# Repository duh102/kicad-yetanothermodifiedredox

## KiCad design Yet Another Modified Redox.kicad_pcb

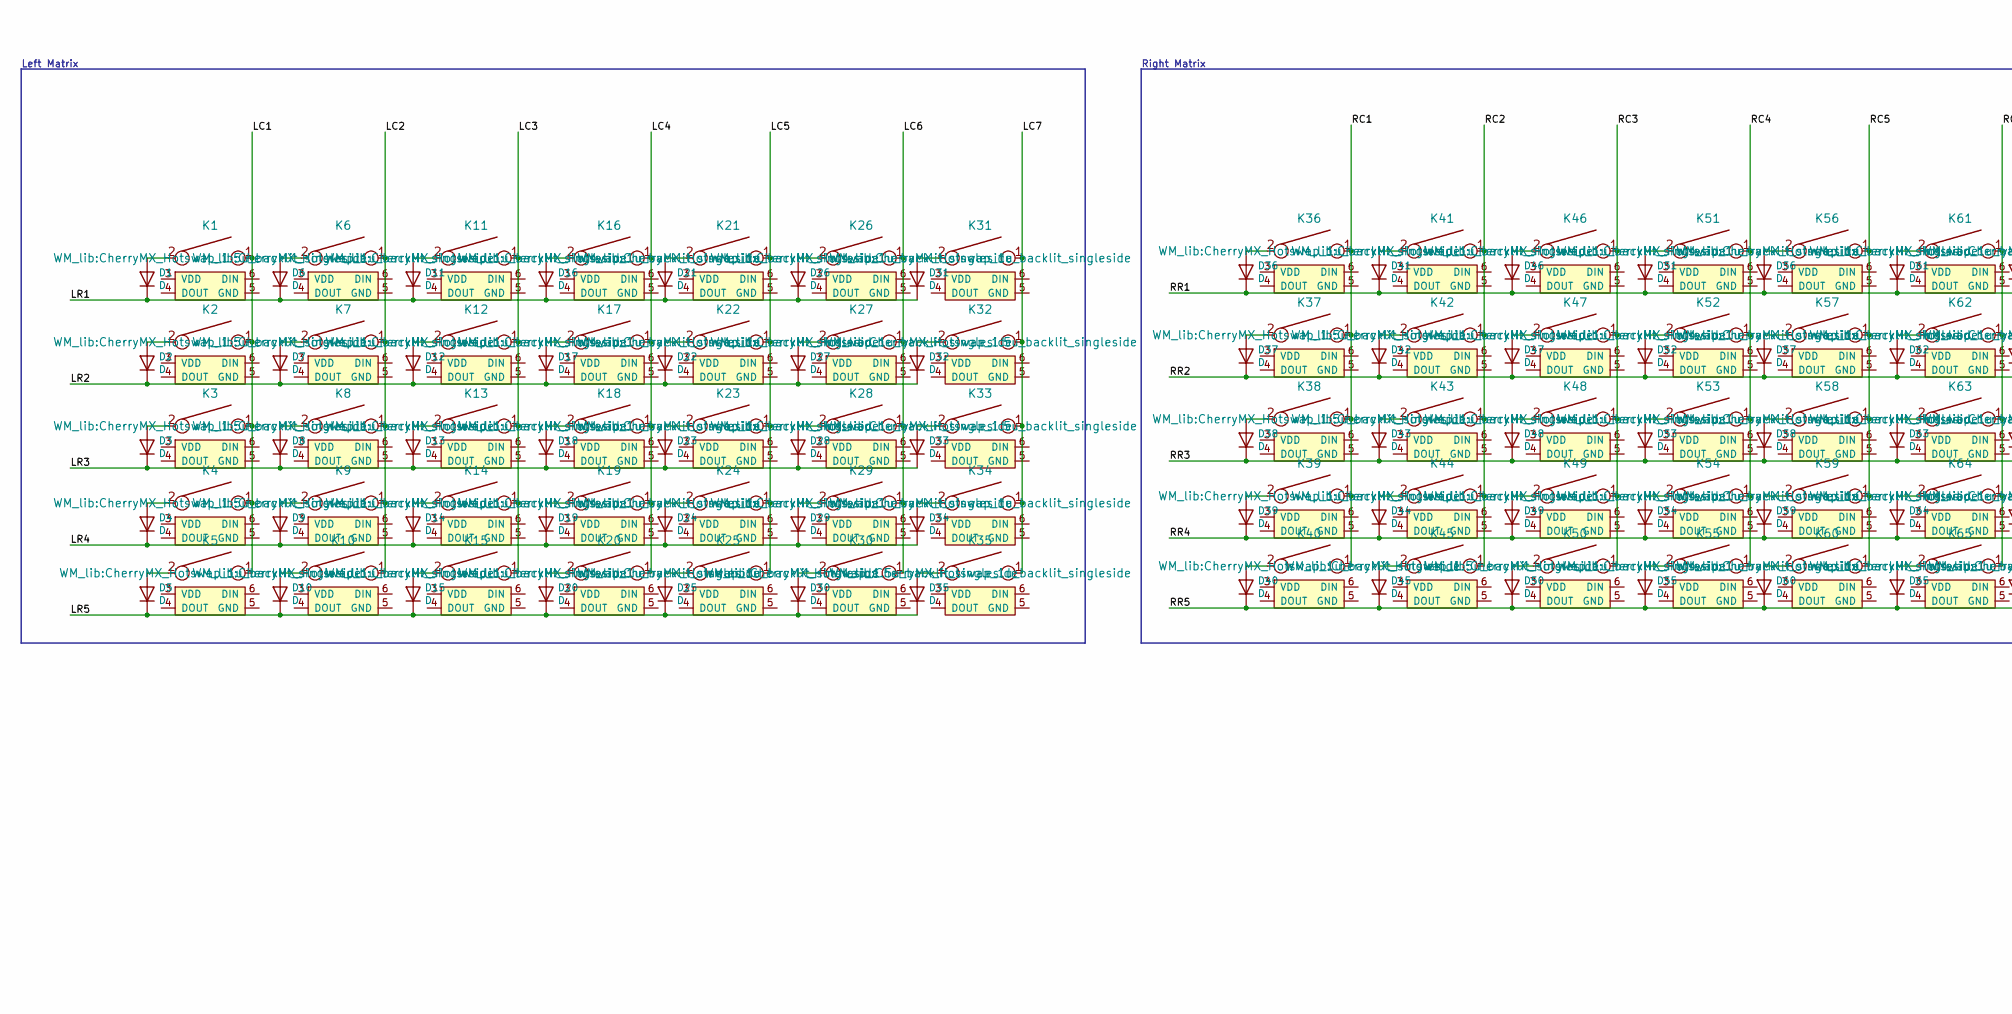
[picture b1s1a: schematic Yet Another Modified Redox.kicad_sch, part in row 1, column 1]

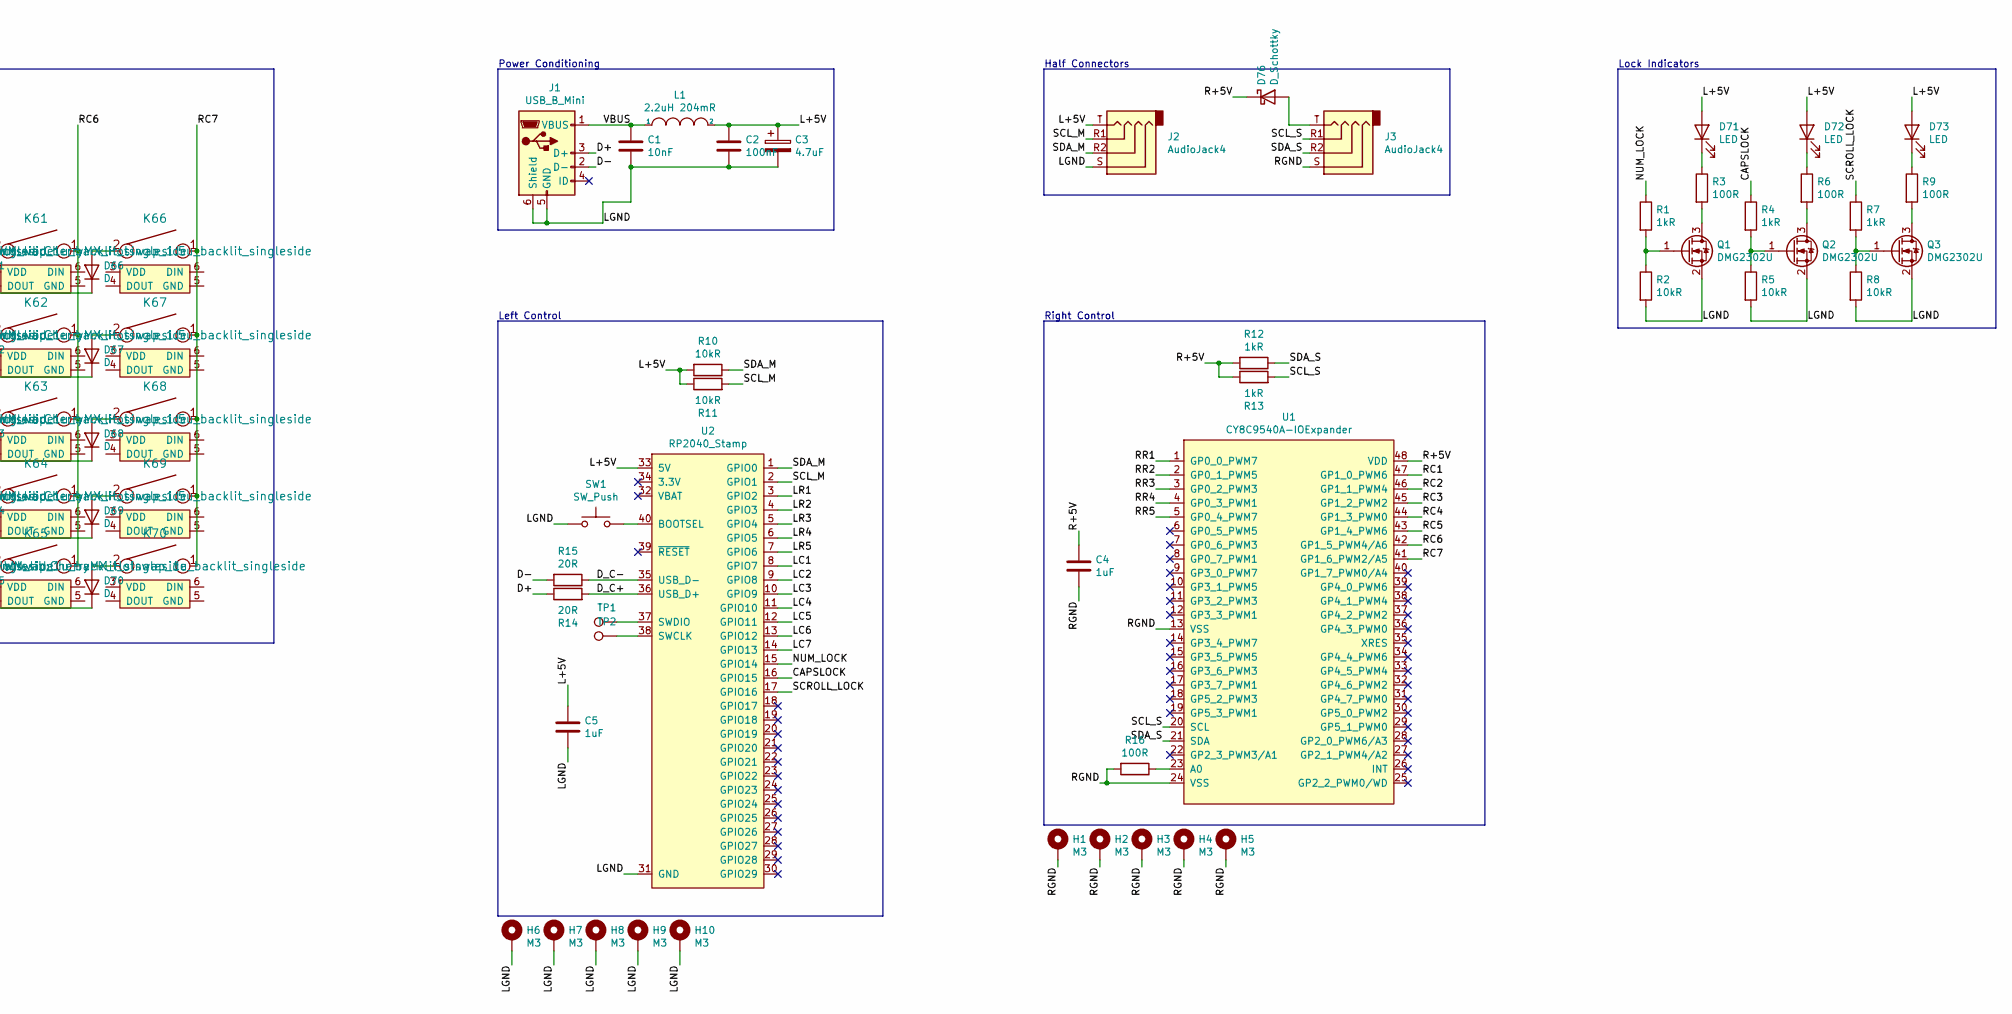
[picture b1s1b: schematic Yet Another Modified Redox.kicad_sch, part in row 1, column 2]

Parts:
C1: 10nF; C_0603_1608Metric
C2: 100nF; C_0603_1608Metric
C3: 4.7uF; CP_Radial_D4.0mm_P2.00mm
C4, C5: 1uF; C_0805_2012Metric
D1, D2, D3, D4, D5, D6, D7, D8, D9, D10, D11, D12, D13, D14, D15, D16, D17, D18, D19, D20, D21, D22, D23, D24, D25, D26, D27, D28, D29, D30, D31, D32, D33, D34, D35, D36, D37, D38, D39, D40, D41, D42, D43, D44, D45, D46, D47, D48, D49, D50, D51, D52, D53, D54, D55, D56, D57, D58, D59, D60, D61, D62, D63, D64, D65, D66, D67, D68, D69, D70: D; D3_TH_SMD_singleside
D71, D72, D73: LED; LED_D3.0mm
D76: D_Schottky; D_SOD-123
H1, H2, H3, H4, H5, H6, H7, H8, H9, H10: M3; MountingHole_3.2mm_M3_ISO14580_Pad
J1: USB_B_Mini; USB_Mini_B_Female_690-005-299-043
J2, J3: AudioJack4; TRRS-PJ-320A
K1, K2, K3, K4, K30, K32, K33, K37, K38, K45, K66, K67, K68, K69: KEYSW; CherryMX_Hotswap_1.5u_backlit_singleside
K5, K6, K7, K8, K9, K10, K11, K12, K13, K14, K15, K16, K17, K18, K19, K20, K21, K22, K23, K24, K25, K26, K27, K28, K29, K31, K34, K35, K36, K39, K40, K41, K42, K43, K44, K46, K47, K48, K49, K50, K51, K52, K53, K54, K55, K56, K57, K58, K59, K60, K61, K62, K63, K64, K65, K70: KEYSW; CherryMX_Hotswap_1u_backlit_singleside
L1: 2.2uH 204mR; L_0805_2012Metric_Pad1.15x1.40mm_HandSolder
Q1, Q2, Q3: DMG2302U; SOT-23
R1, R4, R7, R12, R13: 1kR; R_0805_2012Metric
R2, R5, R8, R10, R11: 10kR; R_0805_2012Metric
R3, R6, R9, R16: 100R; R_0805_2012Metric
R14, R15: 20R; R_0805_2012Metric
SW1: SW_Push; SW_SPST_SKQG_WithoutStem
TP1: TP; TestPoint_Pad_D2.0mm
TP2: TestPoint; TestPoint_Pad_D2.0mm
U1: CY8C9540A-IOExpander; SSOP-48_7.5x15.9mm_P0.635mm
U2: RP2040_Stamp; RP2040_Stamp_SMD

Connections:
/CAPSLOCK: R4.1, U2.16 (GPIO15)
/D+: J1.3 (D+), R14.1
/D-: J1.2 (D-), R15.2
/D_C+: R14.2, U2.36 (USB_D+)
/D_C-: R15.1, U2.35 (USB_D-)
/L+5V: C2.1, C3.1, C5.1, D71.2 (A), D72.2 (A), D73.2 (A), J2.T, L1.2, R10.2, R11.1, U2.33 (5V)
/LC1: K1.1, K2.1, K3.1, K4.1, K5.1, U2.8 (GPIO7)
/LC2: K6.1, K7.1, K8.1, K9.1, K10.1, U2.9 (GPIO8)
/LC3: K11.1, K12.1, K13.1, K14.1, K15.1, U2.10 (GPIO9)
/LC4: K16.1, K17.1, K18.1, K19.1, K20.1, U2.11 (GPIO10)
/LC5: K21.1, K22.1, K23.1, K24.1, K25.1, U2.12 (GPIO11)
/LC6: K26.1, K27.1, K28.1, K29.1, K30.1, U2.13 (GPIO12)
/LC7: K31.1, K32.1, K33.1, K34.1, K35.1, U2.14 (GPIO13)
/LGND: C1.2, C2.2, C3.2, C5.2, H6.1, H7.1, H8.1, H9.1, H10.1, J1.5 (GND), J1.6 (Shield), J2.S, Q1.2 (S), Q2.2 (S), Q3.2 (S), R2.2, R5.2, R8.2, SW1.1, U2.31 (GND)
/LR1: D1.1 (K), D6.1 (K), D11.1 (K), D16.1 (K), D21.1 (K), D26.1 (K), D31.1 (K), U2.3 (GPIO2)
/LR2: D2.1 (K), D7.1 (K), D12.1 (K), D17.1 (K), D22.1 (K), D27.1 (K), D32.1 (K), U2.4 (GPIO3)
/LR3: D3.1 (K), D8.1 (K), D13.1 (K), D18.1 (K), D23.1 (K), D28.1 (K), D33.1 (K), U2.5 (GPIO4)
/LR4: D4.1 (K), D9.1 (K), D14.1 (K), D19.1 (K), D24.1 (K), D29.1 (K), D34.1 (K), U2.6 (GPIO5)
/LR5: D5.1 (K), D10.1 (K), D15.1 (K), D20.1 (K), D25.1 (K), D30.1 (K), D35.1 (K), U2.7 (GPIO6)
/NUM_LOCK: R1.1, U2.15 (GPIO14)
/R+5V: C4.1, D76.1 (K), R12.2, R13.1, U1.48 (VDD)
/RC1: K36.1, K37.1, K38.1, K39.1, K40.1, U1.47 (GP1_0_PWM6)
/RC2: K41.1, K42.1, K43.1, K44.1, K45.1, U1.46 (GP1_1_PWM4)
/RC3: K46.1, K47.1, K48.1, K49.1, K50.1, U1.45 (GP1_2_PWM2)
/RC4: K51.1, K52.1, K53.1, K54.1, K55.1, U1.44 (GP1_3_PWM0)
/RC5: K56.1, K57.1, K58.1, K59.1, K60.1, U1.43 (GP1_4_PWM6)
/RC6: K61.1, K62.1, K63.1, K64.1, K65.1, U1.42 (GP1_5_PWM4/A6)
/RC7: K66.1, K67.1, K68.1, K69.1, K70.1, U1.41 (GP1_6_PWM2/A5)
/RGND: C4.2, H1.1, H2.1, H3.1, H4.1, H5.1, J3.S, R16.2, U1.13 (VSS), U1.24 (VSS)
/RR1: D36.1 (K), D41.1 (K), D46.1 (K), D51.1 (K), D56.1 (K), D61.1 (K), D66.1 (K), U1.1 (GP0_0_PWM7)
/RR2: D37.1 (K), D42.1 (K), D47.1 (K), D52.1 (K), D57.1 (K), D62.1 (K), D67.1 (K), U1.2 (GP0_1_PWM5)
/RR3: D38.1 (K), D43.1 (K), D48.1 (K), D53.1 (K), D58.1 (K), D63.1 (K), D68.1 (K), U1.3 (GP0_2_PWM3)
/RR4: D39.1 (K), D44.1 (K), D49.1 (K), D54.1 (K), D59.1 (K), D64.1 (K), D69.1 (K), U1.4 (GP0_3_PWM1)
/RR5: D40.1 (K), D45.1 (K), D50.1 (K), D55.1 (K), D60.1 (K), D65.1 (K), D70.1 (K), U1.5 (GP0_4_PWM7)
/SCL_M: J2.R1, R11.2, U2.2 (GPIO1)
/SCL_S: J3.R1, R13.2, U1.20 (SCL)
/SCROLL_LOCK: R7.1, U2.17 (GPIO16)
/SDA_M: J2.R2, R10.1, U2.1 (GPIO0)
/SDA_S: J3.R2, R12.1, U1.21 (SDA)
/VBUS: C1.1, J1.1 (VBUS), L1.1
unnamed: D1.2 (A), K1.2
unnamed: D2.2 (A), K2.2
unnamed: D3.2 (A), K3.2
unnamed: D4.2 (A), K4.2
unnamed: D5.2 (A), K5.2
unnamed: D6.2 (A), K6.2
unnamed: D7.2 (A), K7.2
unnamed: D8.2 (A), K8.2
unnamed: D9.2 (A), K9.2
unnamed: D10.2 (A), K10.2
unnamed: D11.2 (A), K11.2
unnamed: D12.2 (A), K12.2
unnamed: D13.2 (A), K13.2
unnamed: D14.2 (A), K14.2
unnamed: D15.2 (A), K15.2
unnamed: D16.2 (A), K16.2
unnamed: D17.2 (A), K17.2
unnamed: D18.2 (A), K18.2
unnamed: D19.2 (A), K19.2
unnamed: D20.2 (A), K20.2
unnamed: D21.2 (A), K21.2
unnamed: D22.2 (A), K22.2
unnamed: D23.2 (A), K23.2
unnamed: D24.2 (A), K24.2
unnamed: D25.2 (A), K25.2
unnamed: D26.2 (A), K26.2
unnamed: D27.2 (A), K27.2
unnamed: D28.2 (A), K28.2
unnamed: D29.2 (A), K29.2
unnamed: D30.2 (A), K30.2
unnamed: D31.2 (A), K31.2
unnamed: D32.2 (A), K32.2
unnamed: D33.2 (A), K33.2
unnamed: D34.2 (A), K34.2
unnamed: D35.2 (A), K35.2
unnamed: D36.2 (A), K36.2
unnamed: D37.2 (A), K37.2
unnamed: D38.2 (A), K38.2
unnamed: D39.2 (A), K39.2
unnamed: D40.2 (A), K40.2
unnamed: D41.2 (A), K41.2
unnamed: D42.2 (A), K42.2
unnamed: D43.2 (A), K43.2
unnamed: D44.2 (A), K44.2
unnamed: D45.2 (A), K45.2
unnamed: D46.2 (A), K46.2
unnamed: D47.2 (A), K47.2
unnamed: D48.2 (A), K48.2
unnamed: D49.2 (A), K49.2
unnamed: D50.2 (A), K50.2
unnamed: D51.2 (A), K51.2
unnamed: D52.2 (A), K52.2
unnamed: D53.2 (A), K53.2
unnamed: D54.2 (A), K54.2
unnamed: D55.2 (A), K55.2
unnamed: D56.2 (A), K56.2
unnamed: D57.2 (A), K57.2
unnamed: D58.2 (A), K58.2
unnamed: D59.2 (A), K59.2
unnamed: D60.2 (A), K60.2
unnamed: D61.2 (A), K61.2
unnamed: D62.2 (A), K62.2
unnamed: D63.2 (A), K63.2
unnamed: D64.2 (A), K64.2
unnamed: D65.2 (A), K65.2
unnamed: D66.2 (A), K66.2
unnamed: D67.2 (A), K67.2
unnamed: D68.2 (A), K68.2
unnamed: D69.2 (A), K69.2
unnamed: D70.2 (A), K70.2
unnamed: D71.1 (K), R3.1
unnamed: D72.1 (K), R6.1
unnamed: D73.1 (K), R9.1
unnamed: D76.2 (A), J3.T
unnamed: Q1.1 (G), R1.2, R2.1
unnamed: Q1.3 (D), R3.2
unnamed: Q2.1 (G), R4.2, R5.1
unnamed: Q2.3 (D), R6.2
unnamed: Q3.1 (G), R7.2, R8.1
unnamed: Q3.3 (D), R9.2
unnamed: R16.1, U1.23 (A0)
unnamed: SW1.2, U2.40 (BOOTSEL)
unnamed: TP1.1, U2.37 (SWDIO)
unnamed: TP2.1, U2.38 (SWCLK)

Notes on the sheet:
Half Connectors
Power Conditioning
Left Control
Right Control
Right Matrix
Lock Indicators
Left Matrix

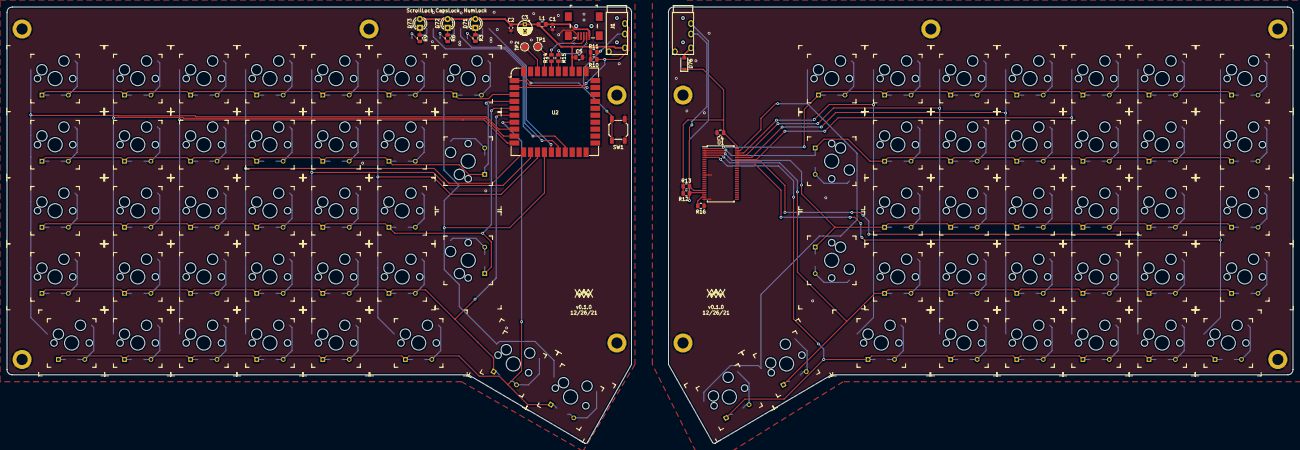
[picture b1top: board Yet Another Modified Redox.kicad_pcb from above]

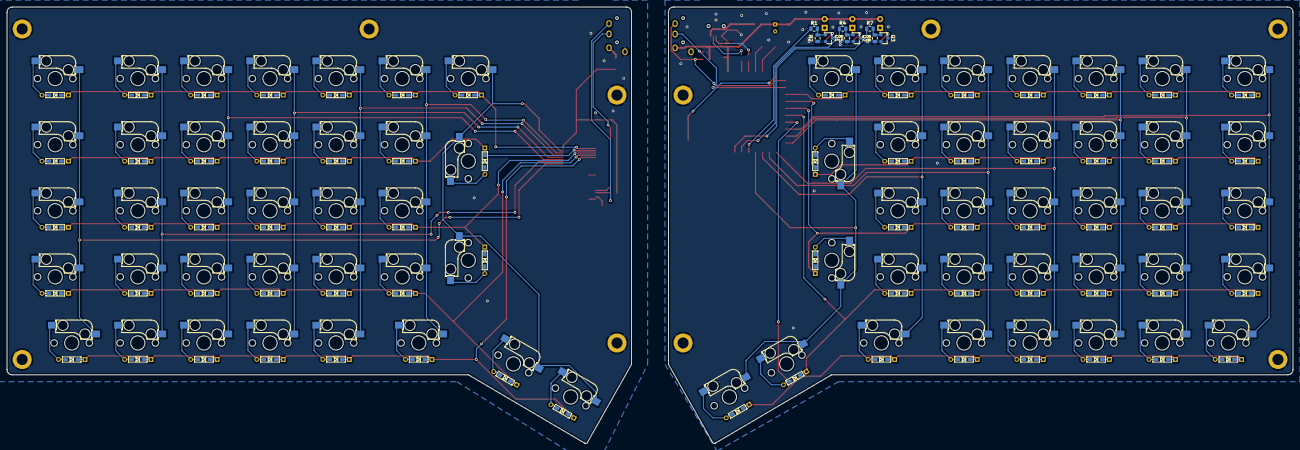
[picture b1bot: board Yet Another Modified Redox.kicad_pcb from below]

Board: 2 copper layers, 370.6 x 125.8 mm, 186 parts (79 on the bottom side), 124 nets.

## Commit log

2021-03-16 Initial commit; v0.0.1
2022-01-28 Update to use rp2040 stamp
